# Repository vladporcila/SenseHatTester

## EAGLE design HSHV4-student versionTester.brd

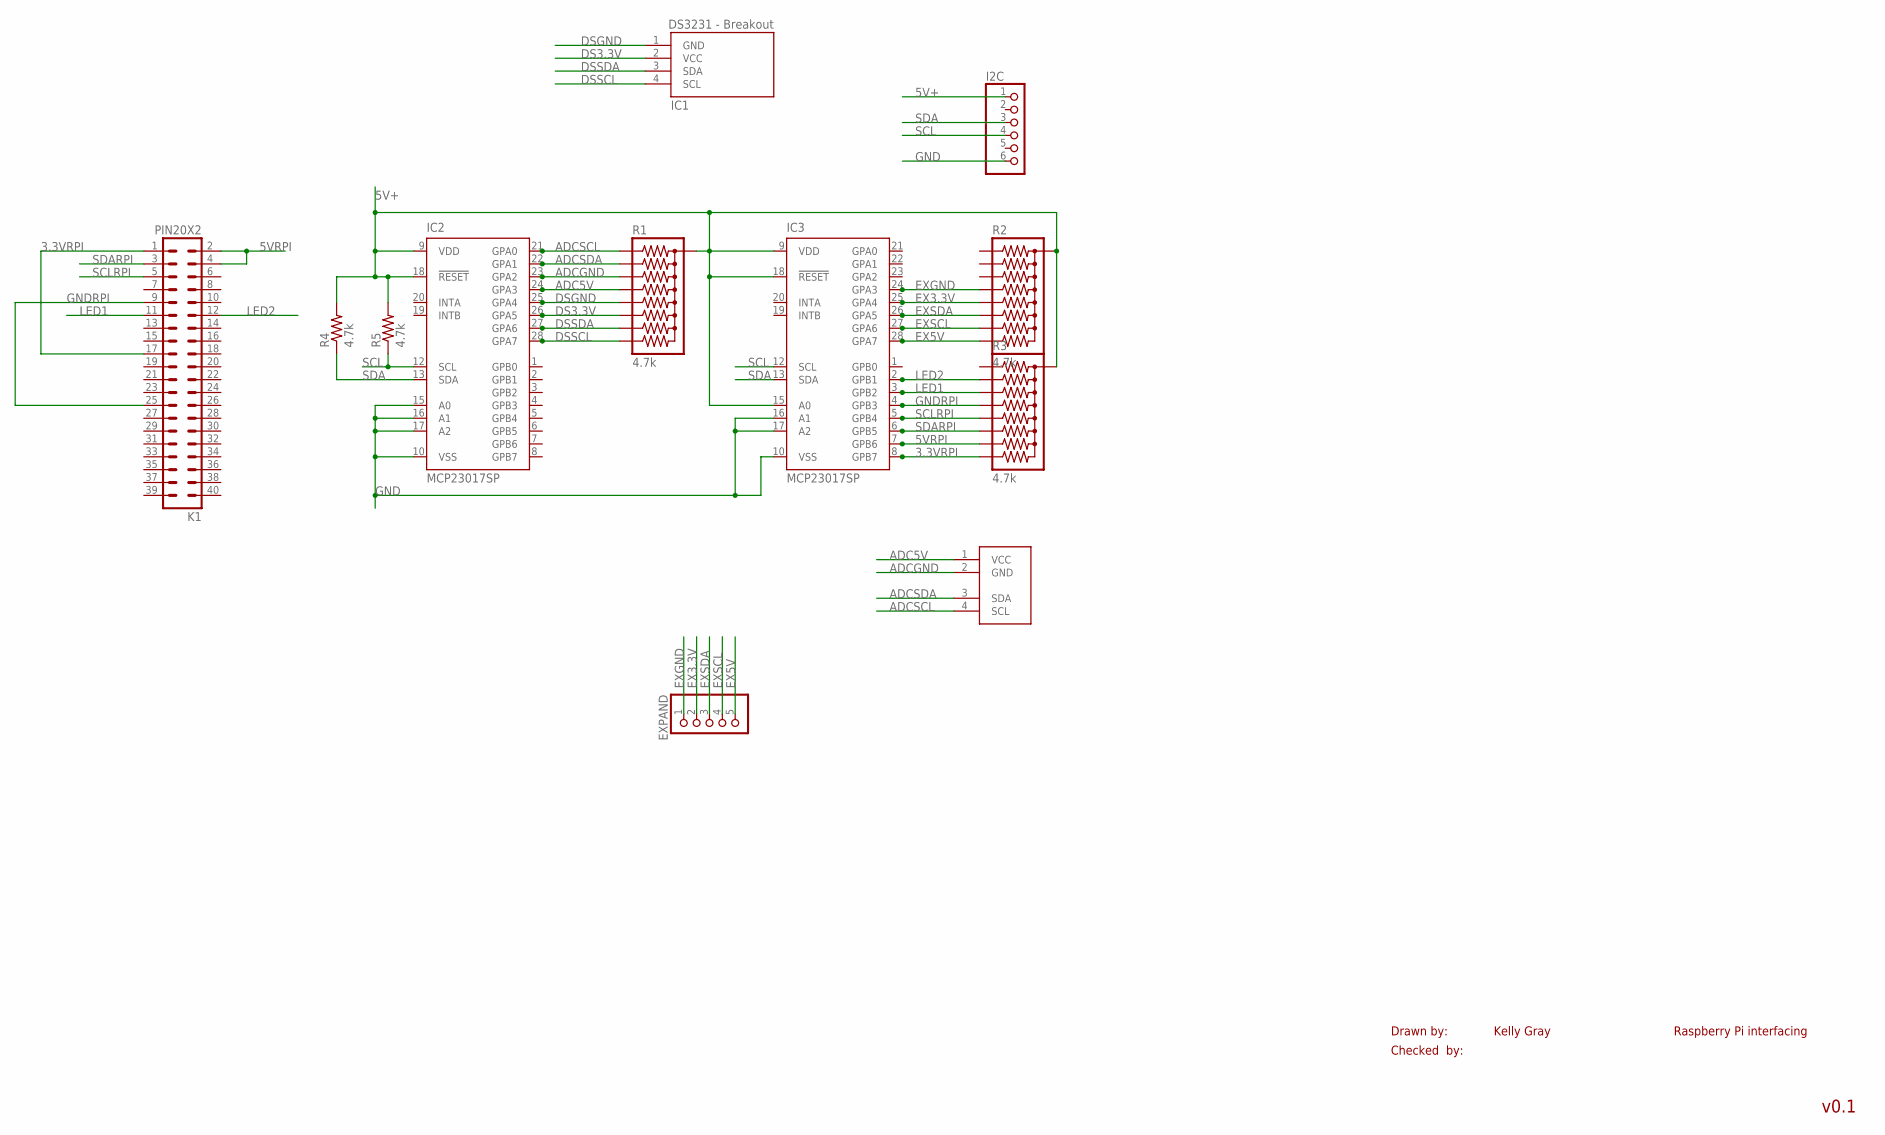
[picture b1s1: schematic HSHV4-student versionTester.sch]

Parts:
EXPAND: PINHD-1X5; 1X05
I2C: PINHD-1X6; 1X06
IC1: DS3231; 8PTH
IC2, IC3: MCP23017SP; DIL28-3
K1: PIN20X2; PIN_20X2
R1, R2, R3: 4.7k; RPACK-SIP-PTH-8
R4, R5: 4.7k; 0414/15
U$1: PCF8591; 1X04

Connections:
3.3VRPI: IC3.8 (GPB7), K1.1, K1.17, R3.P$9 (9)
5V+: I2C.1, IC2.9 (VDD), IC2.18 (!RESET), IC3.9 (VDD), IC3.15 (A0), IC3.18 (!RESET), R1.P$1 (1), R2.P$1 (1), R3.P$1 (1), R4.2, R5.2
5VRPI: IC3.7 (GPB6), K1.2, K1.4, R3.P$8 (8)
ADC5V: IC2.24 (GPA3), R1.P$5 (5), U$1.1 (VCC)
ADCGND: IC2.23 (GPA2), R1.P$4 (4), U$1.2 (GND)
ADCSCL: IC2.21 (GPA0), R1.P$2 (2), U$1.4 (SCL)
ADCSDA: IC2.22 (GPA1), R1.P$3 (3), U$1.3 (SDA)
DS3.3V: IC1.2 (VCC), IC2.26 (GPA5), R1.P$7 (7)
DSGND: IC1.1 (GND), IC2.25 (GPA4), R1.P$6 (6)
DSSCL: IC1.4 (SCL), IC2.28 (GPA7), R1.P$9 (9)
DSSDA: IC1.3 (SDA), IC2.27 (GPA6), R1.P$8 (8)
EX3.3V: EXPAND.2, IC3.25 (GPA4), R2.P$6 (6)
EX5V: EXPAND.5, IC3.28 (GPA7), R2.P$9 (9)
EXGND: EXPAND.1, IC3.24 (GPA3), R2.P$5 (5)
EXSCL: EXPAND.4, IC3.27 (GPA6), R2.P$8 (8)
EXSDA: EXPAND.3, IC3.26 (GPA5), R2.P$7 (7)
GND: I2C.6, IC2.10 (VSS), IC2.15 (A0), IC2.16 (A1), IC2.17 (A2), IC3.10 (VSS), IC3.16 (A1), IC3.17 (A2)
GNDRPI: IC3.4 (GPB3), K1.9, K1.25, R3.P$5 (5)
LED1: IC3.3 (GPB2), K1.11, R3.P$4 (4)
LED2: IC3.2 (GPB1), K1.12, R3.P$3 (3)
SCL: I2C.4, IC2.12 (SCL), IC3.12 (SCL), R5.1
SCLRPI: IC3.5 (GPB4), K1.5, R3.P$6 (6)
SDA: I2C.3, IC2.13 (SDA), IC3.13 (SDA), R4.1
SDARPI: IC3.6 (GPB5), K1.3, R3.P$7 (7)

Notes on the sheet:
Drawn by:
Checked by:
Kelly Gray
v0.1
Raspberry Pi interfacing

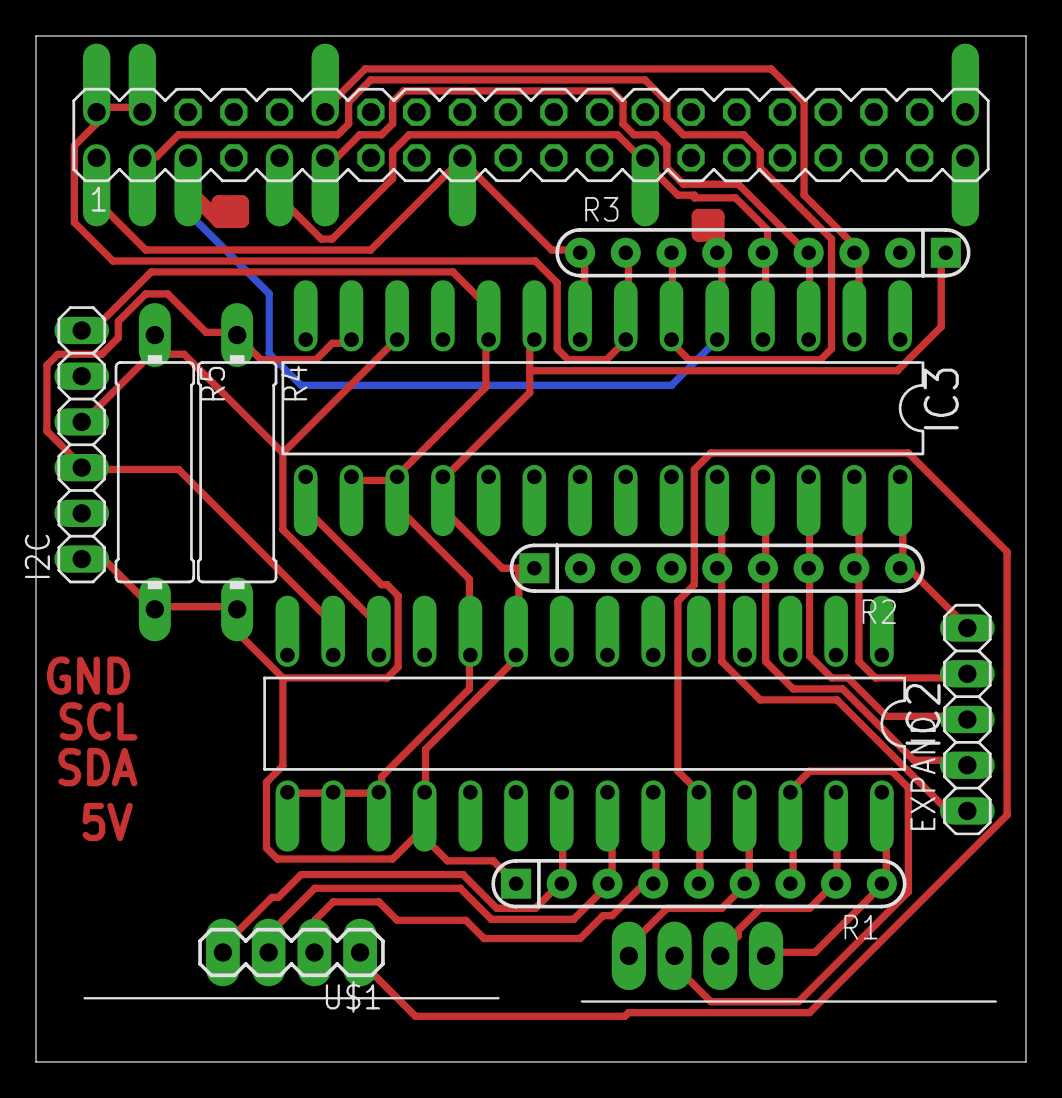
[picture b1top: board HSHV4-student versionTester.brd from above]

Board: 2 copper layers, 55.0 x 57.0 mm, 12 parts (0 on the bottom side), 24 nets.

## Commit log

2016-11-02 :boom::camel: Added .gitattributes & .gitignore files
2016-11-02 SenseHatTester
    SenseHatTester

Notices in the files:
parts and their libraries:
SparkFun-Resistors: Licensing: Creative Commons ShareAlike 4.0 International - https://creativecommons.org/licenses/by-sa/4.0
